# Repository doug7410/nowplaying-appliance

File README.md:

# Now-Playing appliance

A desk device that listens to the room, figures out what song is playing, and shows it:
a HUB75 LED matrix renders a synced spectrum / lyrics visualization, and a 5" touch
screen shows the cover, title, artist, progress and a mosaic of what played recently.
The whole thing lives in a routed guitar body with three gold knobs and a bat-handle
power toggle.

```
                       room audio
                           │
             ┌─────────────▼──────────────┐
             │  BOARD 1 — the room ear     │  ESP32-S3 running a WLED-MM fork:
             │  I2S mic · HUB75 64×32      │  spectrum / Keybeat / lyrics looks,
             │  panel · 3 knobs            │  uploads mic windows to the cloud
             └──────┬───────────────▲──────┘
      POST /ingest  │               │  GET /lyrics
                    │               │              UART (knobs, re-check, heartbeat)
             ┌──────▼───────────────┴──────┐        │
             │  CLOUD — recognition brain   │        │
             │  songrec → now-playing state │        │
             │  → metadata, lyrics, covers  │        │
             └──────┬───────────────▲──────┘        │
     GET /nowplaying│               │ GET /album/{id}│
             ┌──────▼───────────────┴──────┐        │
             │  BOARD 2 — the touch display │◄───────┘
             │  Raspberry Pi + 5" HDMI/USB  │  native LVGL app (display/)
             └─────────────────────────────┘
```

Both boards authenticate to the cloud with **one shared device token**. The cloud
derives all state server-side; the boards render dumb.

## What is in this repo

| Path | What |
|---|---|
| [`BOM.md`](BOM.md) | The full parts list, with prices and sourcing notes |
| [`docs/assembly.md`](docs/assembly.md) | Order the PCBs, solder them, wire the harness, drill the front panel, first power-on |
| [`docs/board1-firmware.md`](docs/board1-firmware.md) | Build, flash and provision the ESP32-S3 "ear" |
| [`docs/board2-display.md`](docs/board2-display.md) | Set up the Raspberry Pi and run the display app |
| [`docs/cloud.md`](docs/cloud.md) | Running the recognition service and minting the shared token |
| `hardware/carrier-board/` | KiCad source + JLCPCB zip for the interconnect PCB (ESP32-S3 socket, power, HUB75, knobs, mic, Pi) |
| `hardware/knob-board/` | KiCad source + zip for the 3-encoder front-panel PCB. Also the front-panel drilling template |
| `hardware/mic-board/` | KiCad source + zip for the INMP441 breakout adapter |
| `hardware/panelboard/` + [`docs/panelboard.md`](docs/panelboard.md) | **The minimal build:** a standalone HUB75 driver board for a stock ESP32-WROOM-32 dev board, runs upstream WLED-MM unmodified. Just the LED matrix, none of the rest |
| `display/` | The Board 2 display app (LVGL, C++). Runs on the Pi via DRM/KMS, and on a desktop as an SDL simulator |

## Build order

Only want the LED spectrum on a panel? Build the [panelboard](docs/panelboard.md)
instead: one small PCB, a $5 ESP32 dev board, upstream WLED-MM, done. The rest of this
list is the full appliance.

1. Read [`BOM.md`](BOM.md) and order everything. The three PCBs are bare boards from
   JLCPCB, roughly $20 for five of each, hand-soldered.
2. [`docs/assembly.md`](docs/assembly.md): solder the boards, make the four cables, wire
   power, mount the panel and screen.
3. [`docs/cloud.md`](docs/cloud.md): stand up the cloud service and create **one** device
   token. Both boards use it.
4. [`docs/board1-firmware.md`](docs/board1-firmware.md): flash the ESP32-S3 and run the
   provisioning script. The panel should light up with the "Mountain" spectrum.
5. [`docs/board2-display.md`](docs/board2-display.md): image the Pi, run `provision.sh`
   in `display/`. Play a song in the room.

## Status and what is not here yet

This is a working one-off appliance and the design for a small hand-built batch. Every
board in `hardware/` has been fabbed and passes ERC/DRC with zero violations; the pin
maps and current budgets are measured on the bench, not estimated.

Two source trees the build depends on are **not published yet**:

- **The Board 1 firmware** is a fork of [WLED-MM](https://github.com/MoonModules/WLED-MM)
  carrying a `room_mic_uploader` usermod, the Keybeat and lyrics looks, and the HUB75 pin
  map. [`docs/board1-firmware.md`](docs/board1-firmware.md) documents the build exactly
  so it can be reproduced once the fork is pushed.
- **The cloud service** (Laravel + `songrec`). Its HTTP contract is documented in
  [`docs/cloud.md`](docs/cloud.md); the display app in `display/` codes against it.

## License

See [`LICENSE`](LICENSE).

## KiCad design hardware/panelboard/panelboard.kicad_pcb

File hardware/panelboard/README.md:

# panelboard

A minimal board whose only job is driving a HUB75 LED matrix.

No mic, no knobs, no display — 5 V in, a HUB75 connector out, and a plug-in
ESP32 dev board on top. It exists because the Now-Playing appliance's Board 1
does HUB75 rendering buried under a lot of other hardware, and it would be nice
to have the panel half on its own board.

- **MCU:** a stock **ESP32-WROOM-32 38-pin dev board** (the narrow Type-C kind,
  DORHEA/HiLetgo/DevKitC-32 — classic ESP32, *not* an S3), dropped into two 1×19
  female headers. USB, RESET/BOOT and the 3.3 V regulator all come with the
  module, so this board carries none of them.
- **Row spacing is 22.86 mm (0.9").** That is the narrow version, and it is
  measured off the board in hand — a 1.0" wide-version clone is one 0.1" grid
  step wider and **will not seat**. Check yours before ordering.
- **Panel drive:** straight 3.3 V logic, no level shifters. That's what Board 1
  does today and it is hardware-verified on a 64×32 panel.
- **Power:** 5 V in on a screw terminal → AOD403 P-FET reverse-polarity
  protection → a second screw terminal that feeds the panel. Panels pull 2–4 A,
  so the 5 V path is 2.5 mm wide throughout.
- 70 × 72 mm, 2 layers, ground pour on both.

## The pin map is the firmware's, not this repo's

The HUB75 GPIO assignment is **WLED-MM's classic-ESP32 default** — the `#else`
branch at the bottom of `wled00/bus_manager.cpp`, which is the ESP32-Trinity /
mrcodetastic map. Wiring to it means the firmware needs no pinout patch at all.
Don't "improve" it here; change it there and follow.

| HUB75 | GPIO | col | | HUB75 | GPIO | col |
|---|---|---|---|---|---|---|
| R1 | 25 | J1 | | A | 23 | J3 |
| G1 | 26 | J1 | | B | 19 | J3 |
| B1 | 27 | J1 | | C | 5 | J3 |
| R2 | 14 | J1 | | D | 17 | J3 |
| G2 | **12** | J1 | | E | 18 | J3 |
| B2 | 13 | J1 | | LAT | 4 | J3 |
| | | | | OE | 15 | J3 |
| | | | | CLK | 16 | J3 |

**All six RGB pins live in the module's J1 column and all eight control pins in
J3.** That is the single fact the whole layout is built on — see below.

**G2 is on IO12, which is the MTDI strapping pin.** It has to read low at reset
or the chip comes up expecting 1.8 V flash, and the panel's ribbon is the only
other thing on that net. `RPD` (10 k to GND) holds it down rather than trusting
the internal pull-down. It lives under the module: lying flat it is ~2.5 mm tall
against ~8.5 mm of socket clearance.

**E is wired**, to IO18. The 64×32 panel doesn't use it (HUB75 pin 8 is ground
there), but the firmware default already says `e = 18`, so a 64×64 panel is a
config change rather than a respin.

GPIO 6–11 are the SPI flash on a classic ESP32 and are left unconnected, as are
IO0/IO2 (strapping), TX0/RX0, and the input-only pins 34–39.

## Firmware: this is not a drop-in for Board 1's build

A plain ESP-WROOM-32 module is **4 MB flash and no PSRAM**. Board 1's WLED-MM
build (`~/Code/WLED-MM` `platformio_override.ini`, `[env:board1]`) pins
`extreme_partitions` — a 3.2 MB app plus a 9 MB filesystem on 16 MB flash — and
that partition table cannot fit here. Build a stock classic-ESP32 WLED-MM target
for this board. A 64×32 DMA framebuffer fits in internal RAM comfortably; 64×64
at high bit depth will not.

## JP1 — pull the shunt before plugging in USB

A dev board's 5 V pin has no reverse-current protection. Leave it tied to a live
panel supply with a USB cable also plugged in and the supply back-feeds the host
port. `JP1` sits in series with the module's 5 V pin so you can break that path;
it is west of the module body so the shunt has headroom.

## Building it

Everything in `board/` is generated. The `.kicad_sch` and `.kicad_pcb` are
committed artifacts, but the generators are the source of truth — edit those.

```
cd board
make all       # regenerate the schematic and the board from generator/*.py
make check     # ERC + DRC with schematic parity, gating on every severity
make zip       # -> panelboard-jlc.zip, ready to upload to jlcpcb.com
make render    # top.png / bottom.png
```

`gen_sch.py` is deterministic (uuid5-derived), so it re-emits the schematic
byte-for-byte. `gen_pcb.py` is not — pcbnew mints fresh UUIDs on every run, so
`make all` rewrites the whole `.kicad_pcb` even when nothing changed. Regenerate
when the design actually changes, not as a habit.

The board is clean at `--severity-all`: 0 errors, 0 warnings, 0 unconnected,
0 parity issues. There is no expected-warning exception to remember.

## Assembly

**Order it as a bare PCB, not PCBA.** Q1 (AOD403, TO-252) is the only surface
mount part on the board and it hand-solders easily; everything else is through
hole. Paying JLC's assembly setup for one FET is not worth it.

| Ref | Part |
|---|---|
| J_ESP_L, J_ESP_R | 1×19 female header, 2.54 mm |
| J_HUB | 2×08 shrouded IDC header, vertical |
| J_PWR, J_PANEL | Phoenix MSTBVA 2,5/2-G, 5.00 mm |
| JP1 | 1×02 male header + shunt |
| Q1 | AOD403 P-FET, TO-252 |
| RG / RPD | 100 k / 10 k axial |
| CB1 / CB2 | 470 µF 16 V radial D8 / 100 nF disc |

Solder `RPD` before the sockets go in — once the module is plugged in you can't
reach it.

## Layout notes worth knowing before you move anything

- **The HUB75 IDC's pin-1 y is 32.43, not a round number.** That puts every IDC
  row exactly on a *gap* between two J1 socket pads, so each even-column control
  signal crosses the pad wall dead straight — no jog, no via, no chance of
  crossing a neighbour. Move the connector off that grid and eight nets get
  much harder.
- **The control bundle puts every horizontal on B.Cu and every vertical on
  F.Cu.** Two horizontals at different y can't collide and neither can two
  verticals at different x, so the eight nets are collision-proof by
  construction — which matters, because the source order and the destination
  order genuinely disagree (E and B invert, and the four odd-column pins have to
  wrap around the west side of the connector). Costs two vias per net in a
  corridor with room to spare.
- **The corridor between the two socket rows is empty on both layers.** That
  free 22.86 mm channel is the one real thing a socketed module buys you over a
  soldered-down WROOM, and the control fan spends all of it.
- **The board's north edge is at y = 18** so the module's antenna end overhangs
  into free air. The antenna straddles pin 1 — about 3 mm either side — so there
  is no way to socket pin 1 *and* keep the board out from under it. Ending the
  board short is cheaper and better than a copper keepout.
- **Zone clearance is 0.25 mm, not 0.30.** At 0.30 the pour cannot squeeze
  between two 2.54 mm-pitch through-hole pads (2.54 − 2×1.15 = 0.24, under the
  0.25 minimum thickness), the socket rows fence it off, and GND pads end up
  stranded on islands. At 0.25 the gap is 0.34 and it flows. JLC's floor for
  2 layers is 0.2, so this still has margin.
- **Both electrolytics stay south of y = 73.8.** The module's USB port overhangs
  its south end at about 10 mm height and a D8 radial cap is ~11 mm tall — put
  one further north and the cable has nowhere to go.
- The IDC's **shroud courtyard is much larger than its pads** (10 × 29 mm). It
  is the real constraint on the west half of the board, not the pin field.

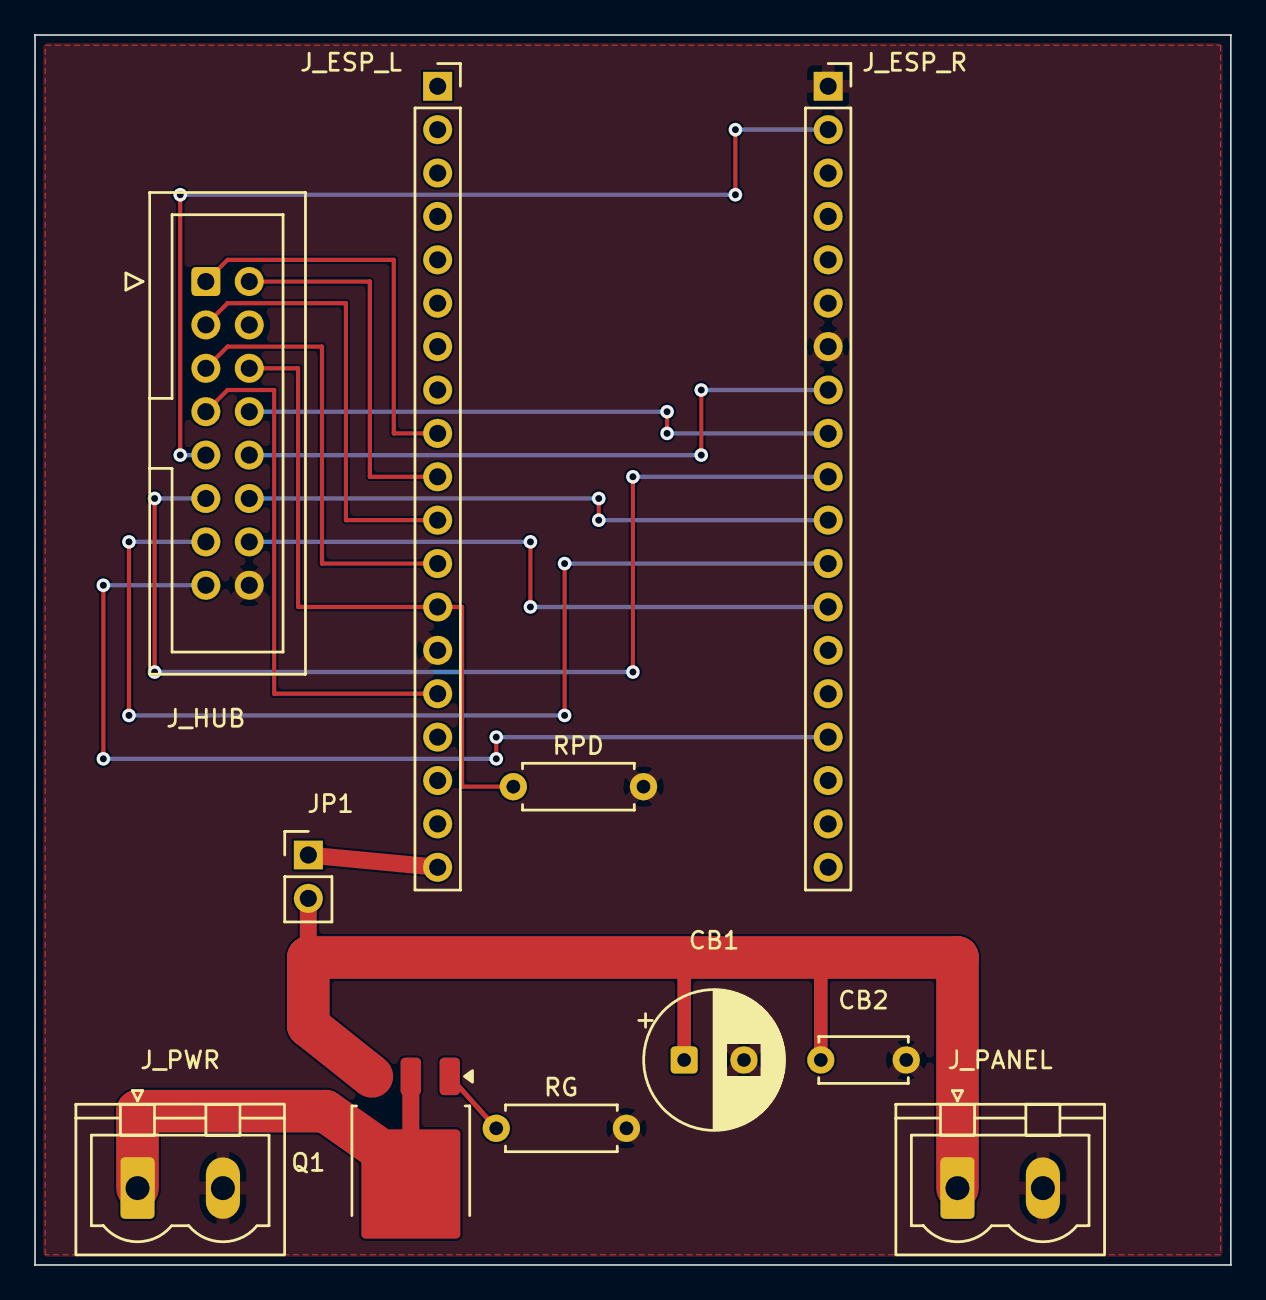
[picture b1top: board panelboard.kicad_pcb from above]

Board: 2 copper layers, 70.0 x 72.0 mm, 11 parts (0 on the bottom side), 19 nets.

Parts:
CB1: 470uF/16V; CP_Radial_D8.0mm_P3.50mm
CB2: 100nF; C_Disc_D5.0mm_W2.5mm_P5.00mm
JP1: ESP 5V; PinHeader_1x02_P2.54mm_Vertical
J_ESP_L: ESP32 J1; PinSocket_1x19_P2.54mm_Vertical
J_ESP_R: ESP32 J3; PinSocket_1x19_P2.54mm_Vertical
J_HUB: HUB75; IDC-Header_2x08_P2.54mm_Vertical
J_PANEL: PANEL 5V; PhoenixContact_MSTBVA_2,5_2-G_1x02_P5.00mm_Vertical
J_PWR: DC IN 5V; PhoenixContact_MSTBVA_2,5_2-G_1x02_P5.00mm_Vertical
Q1: AOD403; TO-252-3_TabPin2
RG: 100k; R_Axial_DIN0207_L6.3mm_D2.5mm_P7.62mm_Horizontal
RPD: 10k; R_Axial_DIN0207_L6.3mm_D2.5mm_P7.62mm_Horizontal

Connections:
/ESP_5V: JP1.1, J_ESP_L.19
/GND: CB1.2, CB2.2, J_ESP_L.14, J_ESP_R.1, J_ESP_R.7, J_HUB.4, J_HUB.16, J_PANEL.2, J_PWR.2, RG.2, RPD.2
/HUB_A: J_ESP_R.2, J_HUB.9
/HUB_B: J_ESP_R.8, J_HUB.10
/HUB_B1: J_ESP_L.11, J_HUB.3
/HUB_B2: J_ESP_L.15, J_HUB.7
/HUB_C: J_ESP_R.10, J_HUB.11
/HUB_CLK: J_ESP_R.12, J_HUB.13
/HUB_D: J_ESP_R.11, J_HUB.12
/HUB_E: J_ESP_R.9, J_HUB.8
/HUB_G1: J_ESP_L.10, J_HUB.2
/HUB_G2: J_ESP_L.13, J_HUB.6, RPD.1
/HUB_LAT: J_ESP_R.13, J_HUB.14
/HUB_OE: J_ESP_R.16, J_HUB.15
/HUB_R1: J_ESP_L.9, J_HUB.1
/HUB_R2: J_ESP_L.12, J_HUB.5
/P5V: CB1.1, CB2.1, JP1.2, J_PANEL.1, Q1.3
/QG: Q1.1, RG.1
/VIN: J_PWR.1, Q1.2

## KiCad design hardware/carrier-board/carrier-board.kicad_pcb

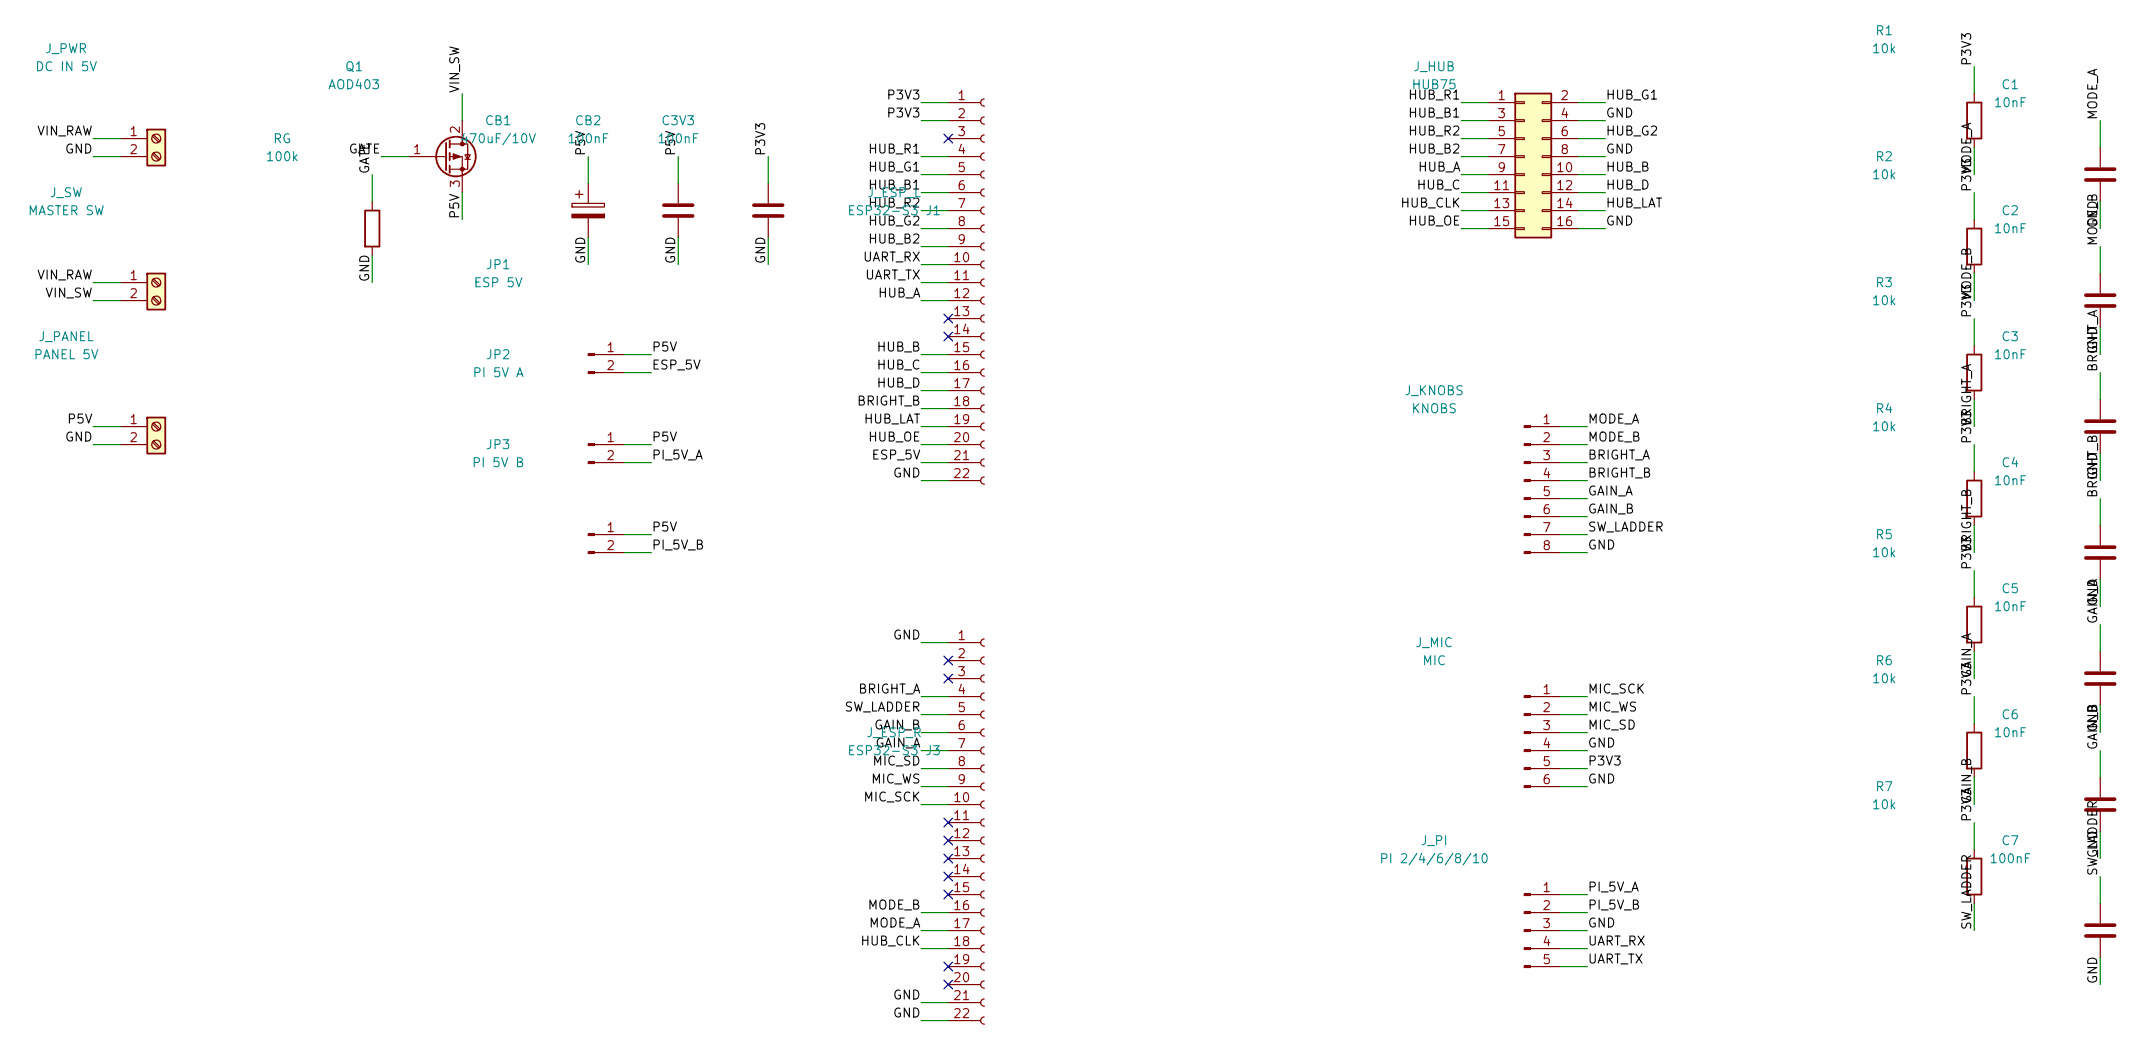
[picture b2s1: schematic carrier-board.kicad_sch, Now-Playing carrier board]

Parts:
C1, C2, C3, C4, C5, C6: 10nF; C_Disc_D5.0mm_W2.5mm_P5.00mm
C3V3, C7: 100nF; C_Disc_D5.0mm_W2.5mm_P5.00mm
CB1: 470uF/10V; CP_Radial_D8.0mm_P3.50mm
CB2: 100nF; C_Disc_D5.0mm_W2.5mm_P5.00mm
JP1: ESP 5V; PinHeader_1x02_P2.54mm_Vertical
JP2: PI 5V A; PinHeader_1x02_P2.54mm_Vertical
JP3: PI 5V B; PinHeader_1x02_P2.54mm_Vertical
J_ESP_L: ESP32-S3 J1; PinSocket_1x22_P2.54mm_Vertical
J_ESP_R: ESP32-S3 J3; PinSocket_1x22_P2.54mm_Vertical
J_HUB: HUB75; IDC-Header_2x08_P2.54mm_Latch_Vertical
J_KNOBS: KNOBS; JST_XH_B8B-XH-A_1x08_P2.50mm_Vertical; MPN B8B-XH-A(LF)(SN)
J_MIC: MIC; JST_XH_B6B-XH-A_1x06_P2.50mm_Vertical; MPN B6B-XH-A(LF)(SN)
J_PANEL: PANEL 5V; PhoenixContact_MSTBVA_2,5_2-G_1x02_P5.00mm_Vertical
J_PI: PI 2/4/6/8/10; JST_XH_B5B-XH-A_1x05_P2.50mm_Vertical; MPN B5B-XH-A(LF)(SN)
J_PWR: DC IN 5V; PhoenixContact_MSTBVA_2,5_2-G_1x02_P5.00mm_Vertical
J_SW: MASTER SW; PhoenixContact_MSTBVA_2,5_2-G_1x02_P5.00mm_Vertical
Q1: AOD403; TO-252-3_TabPin2; MPN AOD403
R1, R2, R3, R4, R5, R6, R7: 10k; R_Axial_DIN0207_L6.3mm_D2.5mm_P7.62mm_Horizontal
RG: 100k; R_Axial_DIN0207_L6.3mm_D2.5mm_P7.62mm_Horizontal

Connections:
/BRIGHT_A: C3.1, J_ESP_R.4, J_KNOBS.3, R3.2
/BRIGHT_B: C4.1, J_ESP_L.18, J_KNOBS.4, R4.2
/ESP_5V: JP1.2, J_ESP_L.21
/GAIN_A: C5.1, J_ESP_R.7, J_KNOBS.5, R5.2
/GAIN_B: C6.1, J_ESP_R.6, J_KNOBS.6, R6.2
/GATE: Q1.1 (G), RG.1
/GND: C1.2, C2.2, C3.2, C3V3.2, C4.2, C5.2, C6.2, C7.2, CB1.2, CB2.2, J_ESP_L.22, J_ESP_R.1, J_ESP_R.21, J_ESP_R.22, J_HUB.4, J_HUB.8, J_HUB.16, J_KNOBS.8, J_MIC.4, J_MIC.6, J_PANEL.2, J_PI.3, J_PWR.2, RG.2
/HUB_A: J_ESP_L.12, J_HUB.9
/HUB_B: J_ESP_L.15, J_HUB.10
/HUB_B1: J_ESP_L.6, J_HUB.3
/HUB_B2: J_ESP_L.9, J_HUB.7
/HUB_C: J_ESP_L.16, J_HUB.11
/HUB_CLK: J_ESP_R.18, J_HUB.13
/HUB_D: J_ESP_L.17, J_HUB.12
/HUB_G1: J_ESP_L.5, J_HUB.2
/HUB_G2: J_ESP_L.8, J_HUB.6
/HUB_LAT: J_ESP_L.19, J_HUB.14
/HUB_OE: J_ESP_L.20, J_HUB.15
/HUB_R1: J_ESP_L.4, J_HUB.1
/HUB_R2: J_ESP_L.7, J_HUB.5
/MIC_SCK: J_ESP_R.10, J_MIC.1
/MIC_SD: J_ESP_R.8, J_MIC.3
/MIC_WS: J_ESP_R.9, J_MIC.2
/MODE_A: C1.1, J_ESP_R.17, J_KNOBS.1, R1.2
/MODE_B: C2.1, J_ESP_R.16, J_KNOBS.2, R2.2
/P3V3: C3V3.1, J_ESP_L.1, J_ESP_L.2, J_MIC.5, R1.1, R2.1, R3.1, R4.1, R5.1, R6.1, R7.1
/P5V: CB1.1, CB2.1, JP1.1, JP2.1, JP3.1, J_PANEL.1, Q1.3 (S)
/PI_5V_A: JP2.2, J_PI.1
/PI_5V_B: JP3.2, J_PI.2
/SW_LADDER: C7.1, J_ESP_R.5, J_KNOBS.7, R7.2
/UART_RX: J_ESP_L.10, J_PI.4
/UART_TX: J_ESP_L.11, J_PI.5
/VIN_RAW: J_PWR.1, J_SW.1
/VIN_SW: J_SW.2, Q1.2 (D)

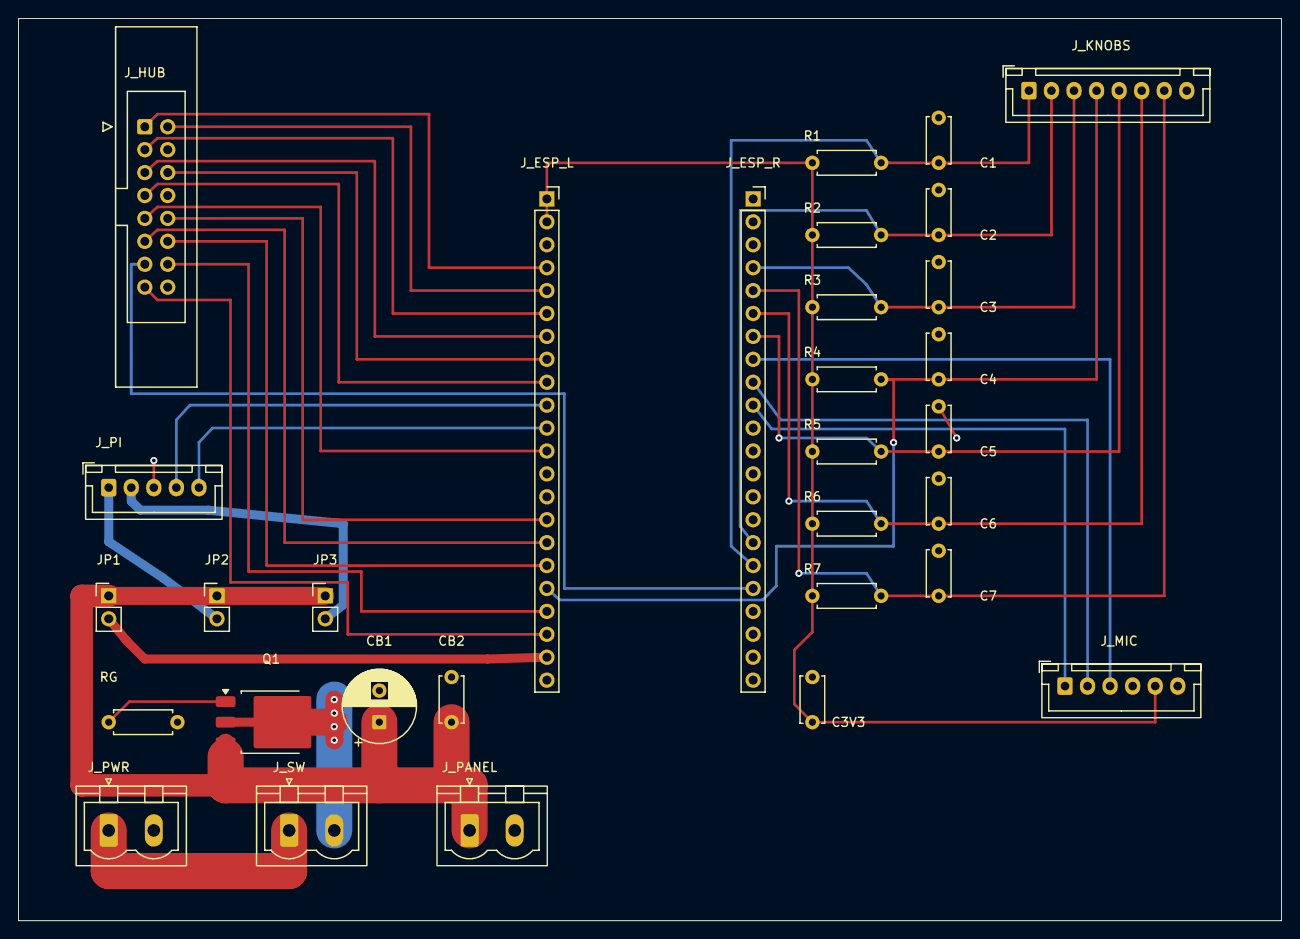
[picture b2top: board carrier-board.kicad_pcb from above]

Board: 2 copper layers, 140.0 x 100.0 mm, 31 parts (0 on the bottom side), 34 nets.

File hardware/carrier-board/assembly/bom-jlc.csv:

Comment,Designator,Footprint,LCSC Part #
AOD403 P-FET,Q1,TO-252-3_TabPin2,C28969
10k axial 1/4W,"R1,R2,R3,R4,R5,R6,R7",R_Axial_DIN0207_P7.62mm,C61299
100k axial 1/4W,RG,R_Axial_DIN0207_P7.62mm,C120103
10nF 50V X7R leaded MLCC,"C1,C2,C3,C4,C5,C6",C_Disc_D5.0mm_P5.00mm,C1620232
100nF 100V X7R leaded MLCC,"C3V3,C7,CB2",C_Disc_D5.0mm_P5.00mm,C1622885
470uF 10V radial D8 P3.5,CB1,CP_Radial_D8.0mm_P3.50mm,C1579341
Screw terminal header 5.00mm 2P (MSTBVA-compatible),"J_PWR,J_SW,J_PANEL","PhoenixContact_MSTBVA_2,5_2-G",C441375
JST B8B-XH-A,J_KNOBS,JST_XH_B8B-XH-A_Vertical,C157972
JST B6B-XH-A,J_MIC,JST_XH_B6B-XH-A_Vertical,C144397
JST B5B-XH-A,J_PI,JST_XH_B5B-XH-A_Vertical,C157991
Pin header 1x2 2.54mm,"JP1,JP2,JP3",PinHeader_1x02_P2.54mm,C32713268
Pin socket 1x22 2.54mm,"J_ESP_L,J_ESP_R",PinSocket_1x22_P2.54mm,C41376161
IDC box header 2x8 2.54mm,J_HUB,IDC-Header_2x08_Latch,C53207556

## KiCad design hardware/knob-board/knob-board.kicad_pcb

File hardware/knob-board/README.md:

# Knob board (KiCad)

The Board-1 front-panel knob PCB: three EC11 rotary encoders (MODE / BRIGHT / GAIN)
plus a switch resistor ladder, out to a single 8-pin JST-XH connector.

This is a **re-creation in KiCad** of the design that was routed in Flux
(`https://www.flux.ai/doug7410/nowplaying-knob-board~ss`). Flux cannot export
`.kicad_pcb`/`.kicad_sch` — only Gerbers, IPC-2581, ODB++, GenCAD and EDIF, none of
which KiCad imports — so the schematic and layout were rebuilt from the Flux Gerber
and IPC-D-356 netlist exports. The KiCad files here are now the source of truth.

## The circuit

Ten nets, six parts. Every footprint is stock KiCad — no custom library.

| Ref | Part | Footprint |
|---|---|---|
| ENC1/2/3 | Alps `EC11E15244G1` | `Rotary_Encoder:RotaryEncoder_Alps_EC11E-Switch_Vertical_H20mm` |
| J1 | JST `B8B-XH-A(LF)(SN)` | `Connector_JST:JST_XH_B8B-XH-A_1x08_P2.50mm_Vertical` |
| R1 | 3.3 kΩ axial | `Resistor_THT:R_Axial_DIN0207_L6.3mm_D2.5mm_P7.62mm_Horizontal` |
| R2 | 10 kΩ axial | same |

**J1 pinout — the harness contract:**

```
1 MODE_A · 2 MODE_B · 3 BRIGHT_A · 4 BRIGHT_B · 5 GAIN_A · 6 GAIN_B · 7 SW_LADDER · 8 GND
```

**The switch ladder.** Three push-switches share one ADC pin. Each switch's common
ties to `SW_LADDER`; the other side goes to GND through a distinct resistance —
ENC1 direct (0 Ω), ENC2 via R1 3.3 kΩ, ENC3 via R2 10 kΩ. The 10 kΩ pull-up to 3V3
and the 100 nF debounce cap live **on the carrier board**, not here; that is why
there is no 3V3 net and the cable is 8 conductors. Levels at GPIO 2 (`ADC1_CH1`):
idle 3.30 V, GAIN 1.65 V, BRIGHT 0.82 V, MODE 0.00 V.

On the KiCad symbol, `A`/`B`/`C` are the rotary section (C is the rotary common →
GND) and `S1`/`S2` are the push-switch. Flux's part model called the same pins
`TERMINAL_A/B/C` and `COM`/`NO`; easy to conflate.

## Geometry

Board **100.0 × 30.0 mm**, rect `(10,10)`–`(110,40)` in KiCad coordinates, centre
`(60,25)`. That frame is deliberately the same one the Flux Gerbers use (Gerber Y is
the negation), so the two can be compared hole-for-hole.

Knob shafts sit at **X = centre −38 / 0 / +38** (38 mm pitch) and **Y = 5 mm above
centre**. The PCB is the front-panel drilling template, so these are the numbers that
have to match the enclosure.

Encoders are on the top layer at 180°; J1, R1 and R2 are on the bottom. The bottom is
a GND pour; the top carries the six quadrature signals.

**Routing.** Pads occupy Y 14.4–25.6 (encoders) and Y 34.59 (J1), leaving a clear
corridor at Y 28–33 across the whole board. Each quadrature signal takes a horizontal
lane there and drops onto its J1 pin; lanes are ordered so no drop ever crosses a lane
still carrying copper at that X. `SW_LADDER` busses all three switch commons and would
have to cross every one of those lanes, so it runs on the **bottom** layer instead —
it just carves a channel through the GND pour, which reconnects around both ends.

## Differences from the Flux board (v2, `a6fcbc93`)

Verified by diffing the drill files:

- **J1, R1, R2 holes are identical** — all 12, exactly.
- **All 15 encoder pins are identical after a deliberate 0.85 mm X shift.** Flux's
  re-route nudged the knob group 0.85 mm right of centre, which broke the left/right
  symmetry (12.85 mm from one edge, 11.15 mm from the other). Here the knobs are
  symmetric: 12.0 mm from each edge.
- **Mounting lugs**: same X, 0.1 mm different in Y, drilled round 2.6 mm vs Flux's
  round 3.0 mm.

This board passes DRC with **0 violations, 0 unconnected pads and 0 schematic-parity
issues**, and JLC's DFM check clean — see below.

## JLC DFM

Ran 2026-08-05 on `knob-board-jlc.zip`: **zero Danger findings in every category** —
no trace/pad spacing, annular ring, edge clearance, soldermask or drill problems.
(The Flux board, by contrast, flagged 21 silkscreen line-width errors, 12
silkscreen-to-pad/hole errors and 11 soldermask-openings-exposing-trace at 0.09 mm.)

Two warnings came back on the first run and are both fixed:

- **Silkscreen line width 0.12 mm (×54).** Stock KiCad footprints ship 0.12 mm silk.
  Everything on F/B.Silkscreen is widened to **0.16 mm** at build time (`SILK_W`), text
  included. Note the exact threshold: **JLC's minimum is 0.153 mm (6 mil), not 0.15** —
  a first attempt at 0.15 mm came back with all 54 warnings intact.
- **Short slot detection 1.3 mm (×6).** The encoder mounting lugs were an oval
  2.8 × 1.5 mm slot; JLC wants a slot at least twice as long as it is wide, and this
  one routed only 1.3 mm. Switched to the stock
  `..._CircularMountingHoles` footprint variant — identical pad positions, but a plain
  round 2.6 mm drill. **The board now has no routed slots at all**, which some fabs
  surcharge for.

If you regenerate the Gerbers, note `make zip` runs `make check` first, so a parity or
DRC regression stops the build rather than silently shipping a stale `gerbers/`.

## Rebuilding

```
make check      # ERC + DRC (with schematic parity); fails on any violation
make gerbers    # gerbers/ + Excellon drill
make zip        # knob-board-jlc.zip — upload this straight to jlcpcb.com
```

`make zip` depends on `check`, so a board that fails DRC can never reach the fab.

**Ordering at JLCPCB:** upload `knob-board-jlc.zip`, then **2 layers, 100 × 30 mm,
1.6 mm, HASL** — every other default is fine. It's a plain 2-layer through-hole board
with no controlled impedance, no blind vias and nothing below 0.35 mm.

Requires `kicad-cli` and the `kicad-library` package (stock symbols and footprints).

Generated output (`gerbers/`, `knob-board-jlc.zip`, `*.rpt`, `*.net`) is gitignored —
the `.kicad_sch` and `.kicad_pcb` are the artifacts that matter.

## Not done

- No silkscreen legend (MODE / BRIGHT / GAIN) next to the knobs — assumed to live on
  the front panel. Say so if the bare board should carry it.
- R1/R2 have no MPN. Irrelevant unless ordering assembly; these are hand-soldered.

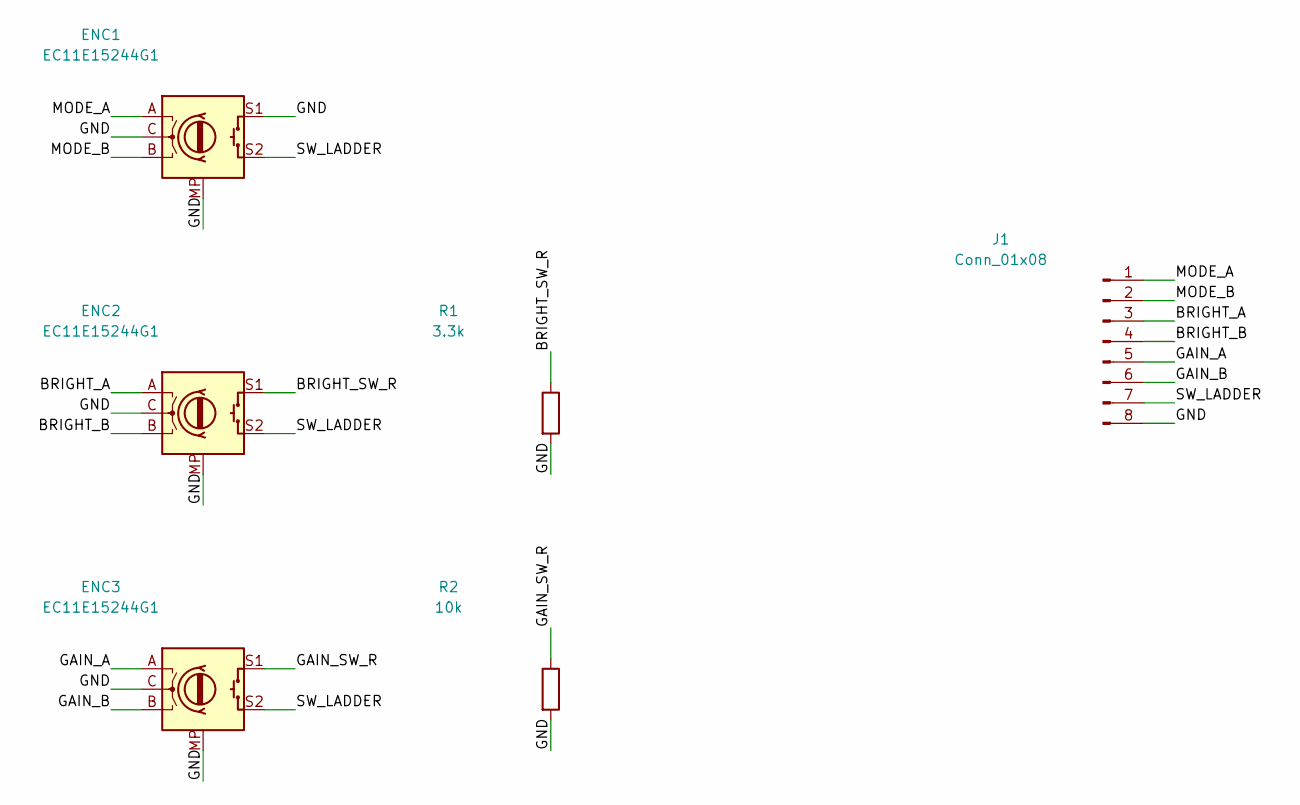
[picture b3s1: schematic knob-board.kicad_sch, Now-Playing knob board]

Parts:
ENC1, ENC2, ENC3: EC11E15244G1; RotaryEncoder_Alps_EC11E-Switch_Vertical_H20mm_CircularMoun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; MPN EC11E15244G1
J1: Conn_01x08; JST_XH_B8B-XH-A_1x08_P2.50mm_Vertical; MPN B8B-XH-A(LF)(SN)
R1: 3.3k; R_Axial_DIN0207_L6.3mm_D2.5mm_P7.62mm_Horizontal
R2: 10k; R_Axial_DIN0207_L6.3mm_D2.5mm_P7.62mm_Horizontal

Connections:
/BRIGHT_A: ENC2.A, J1.3
/BRIGHT_B: ENC2.B, J1.4
/BRIGHT_SW_R: ENC2.S1, R1.1
/GAIN_A: ENC3.A, J1.5
/GAIN_B: ENC3.B, J1.6
/GAIN_SW_R: ENC3.S1, R2.1
/GND: ENC1.C, ENC1.MP, ENC1.S1, ENC2.C, ENC2.MP, ENC3.C, ENC3.MP, J1.8, R1.2, R2.2
/MODE_A: ENC1.A, J1.1
/MODE_B: ENC1.B, J1.2
/SW_LADDER: ENC1.S2, ENC2.S2, ENC3.S2, J1.7

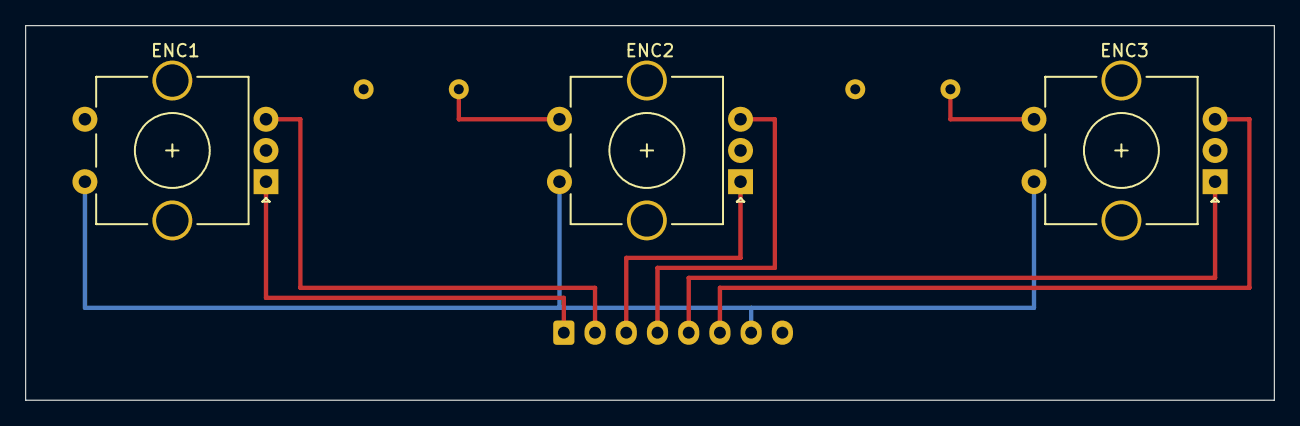
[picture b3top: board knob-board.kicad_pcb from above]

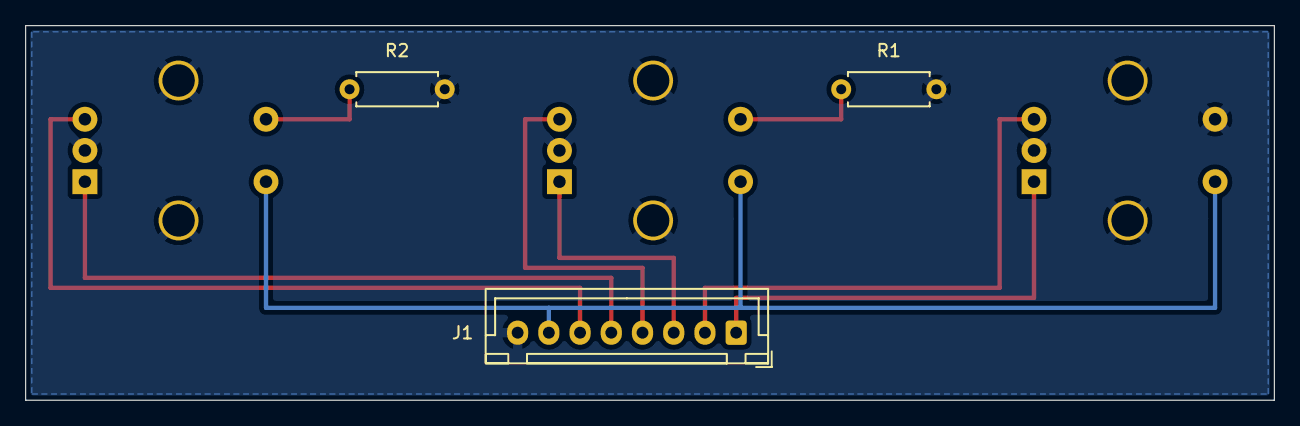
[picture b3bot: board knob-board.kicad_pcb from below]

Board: 2 copper layers, 100.0 x 30.0 mm, 6 parts (3 on the bottom side), 10 nets.

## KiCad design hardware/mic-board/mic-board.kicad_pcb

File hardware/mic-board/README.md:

# Now-Playing mic board

Adapter that mounts the proven round **INMP441 I2S MEMS breakout** (Ø14 mm, two
1×3 rows at 7.62 mm) and brings it out to a **6-pin JST-XH** matching the carrier
board's `J_MIC` pinout, 1:1 cable:

| J1 pin | Net | | J1 pin | Net |
|---|---|---|---|---|
| 1 | MIC_SCK | | 4 | GND |
| 2 | MIC_WS | | 5 | P3V3 |
| 3 | MIC_SD | | 6 | GND |

- **L/R is tied to GND on this board** (left channel) — matches WLED-MM
  `digitalmic.type=1` and the Board 1 smoketest wiring.
- Mount the module **label/port side up** (chip side toward this board) on the
  supplied pin headers; the adapter's silk row labels then match the module's.
  The Ø3 mm center hole is acoustic relief so either mounting orientation works.
- Two M3 holes, 14 mm apart, at the top corners.

Built headlessly (kicad-cli 10); `make check` runs ERC + DRC (0 violations,
schematic parity clean), `make zip` builds `mic-board-jlc.zip` for JLCPCB
(2 layers, 20 × 38 mm, 1.6 mm, HASL — bare board, hand-solder the two headers
and the XH).

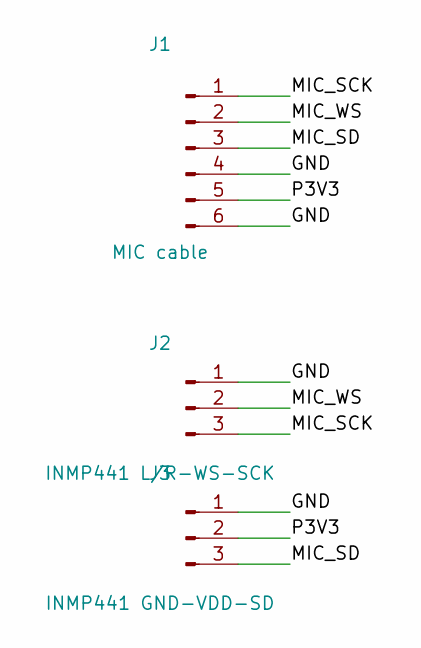
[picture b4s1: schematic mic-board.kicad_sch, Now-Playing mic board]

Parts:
J1: MIC cable; JST_XH_B6B-XH-A_1x06_P2.50mm_Vertical; MPN B6B-XH-A(LF)(SN)
J2: INMP441 L/R-WS-SCK; PinHeader_1x03_P2.54mm_Vertical
J3: INMP441 GND-VDD-SD; PinHeader_1x03_P2.54mm_Vertical

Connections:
/GND: J1.4, J1.6, J2.1, J3.1
/MIC_SCK: J1.1, J2.3
/MIC_SD: J1.3, J3.3
/MIC_WS: J1.2, J2.2
/P3V3: J1.5, J3.2

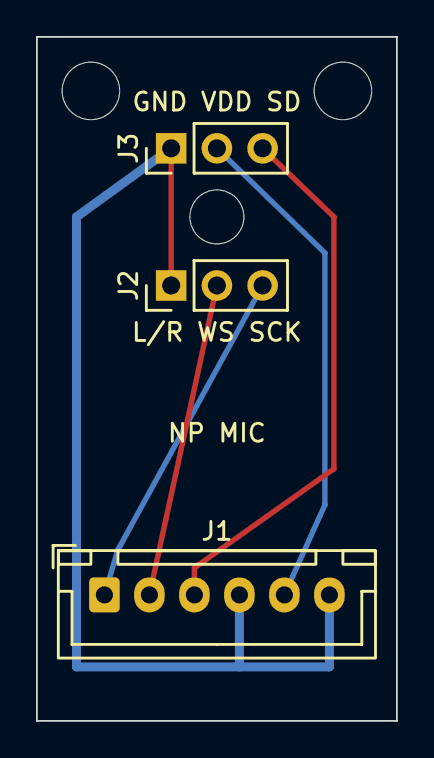
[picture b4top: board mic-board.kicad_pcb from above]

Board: 2 copper layers, 20.0 x 38.0 mm, 6 parts (0 on the bottom side), 5 nets.

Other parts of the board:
H1, H2, H3: (no value)

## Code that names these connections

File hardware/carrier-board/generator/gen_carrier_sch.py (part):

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# (1.0") and will NOT seat in this board -- it is one 0.1" grid step wider.
ESP_L = {  # J1
    "1": "P3V3", "2": "P3V3", "3": NC,            # 3V3, 3V3, RST
    "4": "HUB_R1", "5": "HUB_G1", "6": "HUB_B1",  # GPIO 4, 5, 6
    "7": "HUB_R2", "8": "HUB_G2", "9": "HUB_B2",  # GPIO 7, 15, 16
    "10": "UART_RX", "11": "UART_TX",             # GPIO 17 RX, 18 TX  <-- NOT reversed
    "12": "HUB_A",                                # GPIO 8
    "13": NC, "14": NC,                           # GPIO 3, 46 -- forbidden
    "15": "HUB_B", "16": "HUB_C", "17": "HUB_D",  # GPIO 9, 10, 11
    "18": "BRIGHT_B",                             # GPIO 12
    "19": "HUB_LAT", "20": "HUB_OE",              # GPIO 13, 14
    "21": "ESP_5V", "22": "GND",
}
ESP_R = {  # J3
    "1": "GND", "2": NC, "3": NC,                 # G, U0TXD, U0RXD
    "4": "BRIGHT_A", "5": "SW_LADDER",            # GPIO 1, 2 (ADC1_CH1)
    "6": "GAIN_B", "7": "GAIN_A",                 # GPIO 42, 41
    "8": "MIC_SD", "9": "MIC_WS", "10": "MIC_SCK",# GPIO 40, 39, 38
    "11": NC, "12": NC, "13": NC,                 # GPIO 37, 36, 35 -- dead on N16R8
    "14": NC, "15": NC,                           # GPIO 0, 45 -- forbidden
    "16": "MODE_B", "17": "MODE_A",               # GPIO 48, 47
    "18": "HUB_CLK",                              # GPIO 21
    "19": NC, "20": NC,                           # GPIO 20, 19 -- USB D+/D-
    "21": "GND", "22": "GND",
}
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    ("J_MIC", "Connector:Conn_01x06_Pin", 176 * G, 90 * G, "MIC", FP_XH6, "B6B-XH-A(LF)(SN)",
     {"1": "MIC_SCK", "2": "MIC_WS", "3": "MIC_SD", "4": "GND", "5": "P3V3", "6": "GND"}),
    # Pins map 1:1 onto Raspberry Pi header pins 2, 4, 6, 8, 10 in order -- the cable is
    # straight through, no crossing.  UART_RX takes the Pi's TXD (pin 8) and UART_TX feeds
    # the Pi's RXD (pin 10): the crossover happens here, once, and nowhere else.
    # ponytail: GND is one XH contact (3A rated) carrying both 5V legs' return.  A Pi 4 +
    # SSD measures ~1.2A, so 2.5x margin; if a future load pushes past ~2A sustained, the
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
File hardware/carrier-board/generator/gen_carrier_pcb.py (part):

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        via(board, "VIN_SW", 45, y)
    track(board, "VIN_SW", T, (45, 85.5), (45, 90), width=2.0)
    track(board, "VIN_SW", T, (45, 88), (40, 88), width=3.0)     # via farm → tab
    track(board, "VIN_SW", T, (32.96, 88), (37, 88), width=1.0)  # pin 2 → tab strap
    track(board, "GATE", T, (32.96, 85.72), (22.3, 85.72), (20, 88))
    track(board, "ESP_5V", T, (20, 76.54), (22, 79), (24, 81), (62, 81),
          (68.57, 80.80), width=1.0)
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          (27.5, 62))
    track(board, "UART_TX", B, (68.57, 55.40), (31.5, 55.40), (30, 57),
          (30, 62))
    # -- P3V3: over the antenna end, then the resistor bus down x=98;
    # jog west at y 78-88 around C3V3.2 (GND, sits on the bus line) --
    track(board, "P3V3", T, (68.57, 32.54), (68.57, 26), (98, 26))
    track(board, "P3V3", T, (98, 26), (98, 78), (96, 80), (96, 86), (98, 88))
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        track(board, name, T, (91.43, ey), (ex, ey), (ex, vy))
        via(board, name, ex, vy)
        track(board, name, B, (ex, vy), (104, vy), (105.62, ry))
    # BRIGHT_B: from ESP_L.18 slip the R-header pins 18/19, wrap the SE on
    # bottom, one via to hop the mic runs into row 50 from the east
    track(board, "BRIGHT_B", B, (68.57, 73.18), (70, 74.45), (92.5, 74.45),
          (94, 72.9), (94, 68.5), (107, 68.5), (107, 57.0))
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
